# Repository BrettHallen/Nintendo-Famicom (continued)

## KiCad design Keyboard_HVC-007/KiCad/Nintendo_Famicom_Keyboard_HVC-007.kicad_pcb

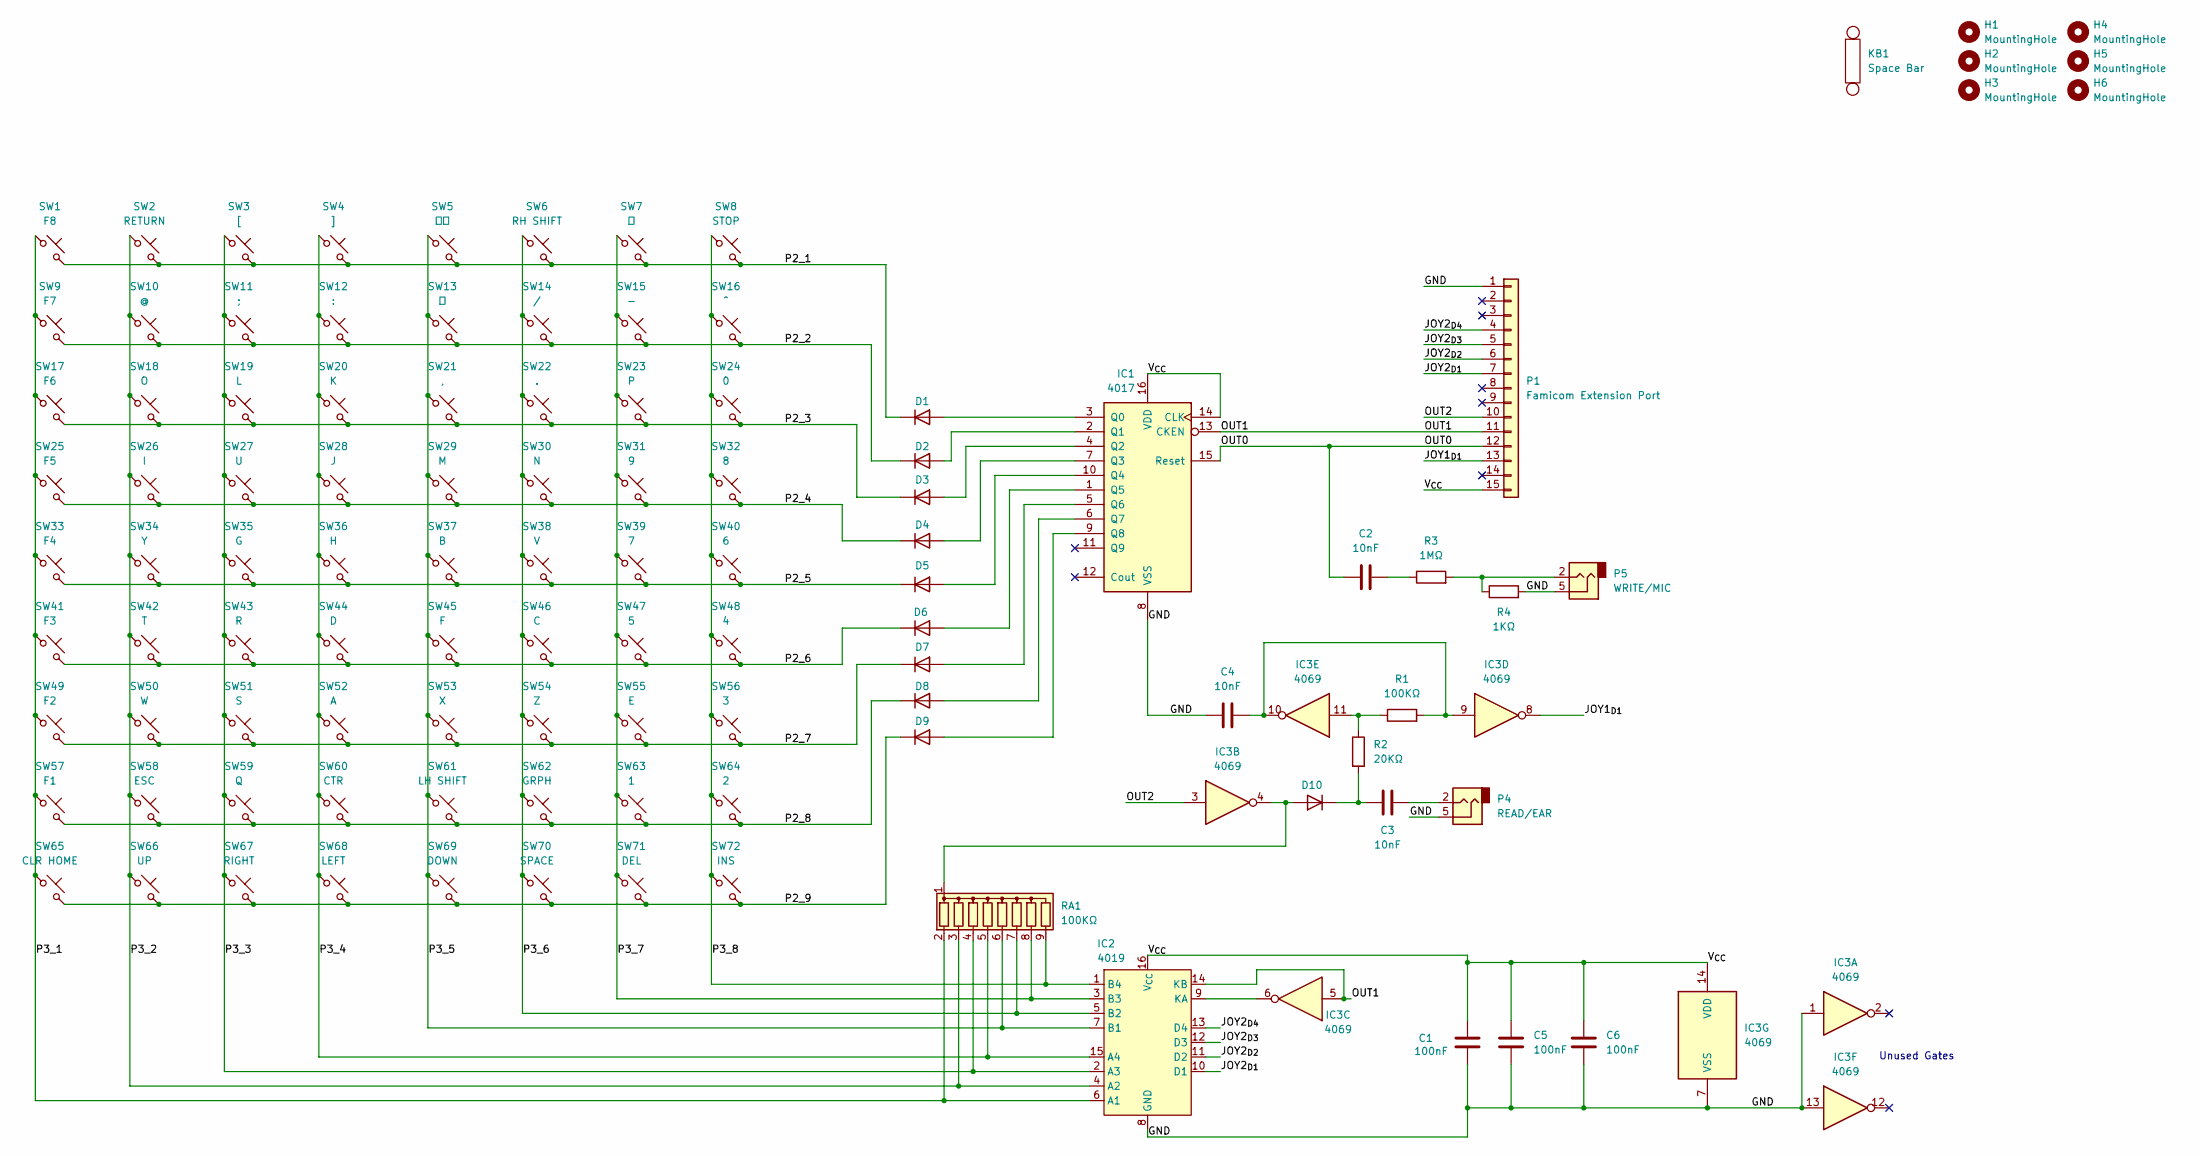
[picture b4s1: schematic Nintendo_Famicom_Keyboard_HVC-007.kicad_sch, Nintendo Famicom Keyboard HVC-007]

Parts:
C1, C5, C6: 100nF; C_Axial_L3.8mm_D2.6mm_P7.50mm_Horizontal
C2, C3, C4: 10nF; C_Axial_L3.8mm_D2.6mm_P7.50mm_Horizontal
D1, D2, D3, D4, D5, D6, D7, D8, D9, D10: 1N4148; D_DO-35_SOD27_P7.62mm_Horizontal
H1, H2, H3, H4, H5, H6: MountingHole; MountingHole_3.2mm_M3
IC1: 4017; DIP-16_W7.62mm
IC2: 4019; DIP-16_W7.62mm
IC3: 4069; DIP-14_W7.62mm
KB1: Space Bar; Stabilizer_Cherry_MX_7.00u
P1: Famicom Extension Port; 57478374
P4: READ/EAR; SJ3350820BTR
P5: WRITE/MIC; SJ3350820BTR
R1: 100KΩ; R_Axial_DIN0207_L6.3mm_D2.5mm_P10.16mm_Horizontal
R2: 20KΩ; R_Axial_DIN0207_L6.3mm_D2.5mm_P10.16mm_Horizontal
R3: 1MΩ; R_Axial_DIN0207_L6.3mm_D2.5mm_P10.16mm_Horizontal
R4: 1KΩ; R_Axial_DIN0207_L6.3mm_D2.5mm_P10.16mm_Horizontal
RA1: 100KΩ; R_Array_SIP9
SW1: F8; SW_Cherry_MX_PCB_2.00u
SW2: RETURN; SW_Cherry_MX_PCB_2.00u
SW3: [; SW_Cherry_MX_PCB_1.00u
SW4: ]; SW_Cherry_MX_PCB_1.00u
SW5: カナ; SW_Cherry_MX_PCB_1.00u
SW6: RH SHIFT; SW_Cherry_MX_PCB_2.00u
SW7: ￥; SW_Cherry_MX_PCB_1.00u
SW8: STOP; SW_Cherry_MX_PCB_1.00u
SW9: F7; SW_Cherry_MX_PCB_2.00u
SW10: @; SW_Cherry_MX_PCB_1.00u
SW11: ;; SW_Cherry_MX_PCB_1.00u
SW12: :; SW_Cherry_MX_PCB_1.00u
SW13: ン; SW_Cherry_MX_PCB_1.00u
SW14: /; SW_Cherry_MX_PCB_1.00u
SW15: -; SW_Cherry_MX_PCB_1.00u
SW16: ^; SW_Cherry_MX_PCB_1.00u
SW17: F6; SW_Cherry_MX_PCB_2.00u
SW18: O; SW_Cherry_MX_PCB_1.00u
SW19: L; SW_Cherry_MX_PCB_1.00u
SW20: K; SW_Cherry_MX_PCB_1.00u
SW21: ,; SW_Cherry_MX_PCB_1.00u
SW22: .; SW_Cherry_MX_PCB_1.00u
SW23: P; SW_Cherry_MX_PCB_1.00u
SW24: 0; SW_Cherry_MX_PCB_1.00u
SW25: F5; SW_Cherry_MX_PCB_2.00u
SW26: I; SW_Cherry_MX_PCB_1.00u
SW27: U; SW_Cherry_MX_PCB_1.00u
SW28: J; SW_Cherry_MX_PCB_1.00u
SW29: M; SW_Cherry_MX_PCB_1.00u
SW30: N; SW_Cherry_MX_PCB_1.00u
SW31: 9; SW_Cherry_MX_PCB_1.00u
SW32: 8; SW_Cherry_MX_PCB_1.00u
SW33: F4; SW_Cherry_MX_PCB_2.00u
SW34: Y; SW_Cherry_MX_PCB_1.00u
SW35: G; SW_Cherry_MX_PCB_1.00u
SW36: H; SW_Cherry_MX_PCB_1.00u
SW37: B; SW_Cherry_MX_PCB_1.00u
SW38: V; SW_Cherry_MX_PCB_1.00u
SW39: 7; SW_Cherry_MX_PCB_1.00u
SW40: 6; SW_Cherry_MX_PCB_1.00u
SW41: F3; SW_Cherry_MX_PCB_2.00u
SW42: T; SW_Cherry_MX_PCB_1.00u
SW43: R; SW_Cherry_MX_PCB_1.00u
SW44: D; SW_Cherry_MX_PCB_1.00u
SW45: F; SW_Cherry_MX_PCB_1.00u
SW46: C; SW_Cherry_MX_PCB_1.00u
SW47: 5; SW_Cherry_MX_PCB_1.00u
SW48: 4; SW_Cherry_MX_PCB_1.00u
SW49: F2; SW_Cherry_MX_PCB_2.00u
SW50: W; SW_Cherry_MX_PCB_1.00u
SW51: S; SW_Cherry_MX_PCB_1.00u
SW52: A; SW_Cherry_MX_PCB_1.00u
SW53: X; SW_Cherry_MX_PCB_1.00u
SW54: Z; SW_Cherry_MX_PCB_1.00u
SW55: E; SW_Cherry_MX_PCB_1.00u
SW56: 3; SW_Cherry_MX_PCB_1.00u
SW57: F1; SW_Cherry_MX_PCB_2.00u
SW58: ESC; SW_Cherry_MX_PCB_1.00u
SW59: Q; SW_Cherry_MX_PCB_1.00u
SW60: CTR; SW_Cherry_MX_PCB_1.00u
SW61: LH SHIFT; SW_Cherry_MX_PCB_2.00u
SW62: GRPH; SW_Cherry_MX_PCB_1.00u
SW63: 1; SW_Cherry_MX_PCB_1.00u
SW64: 2; SW_Cherry_MX_PCB_1.00u
SW65: CLR HOME; SW_Cherry_MX_PCB_1.00u
SW66: UP; SW_Cherry_MX_PCB_2.00u
SW67: RIGHT; SW_Cherry_MX_PCB_2.00u
SW68: LEFT; SW_Cherry_MX_PCB_2.00u
SW69: DOWN; SW_Cherry_MX_PCB_2.00u
SW70: SPACE; SW_Cherry_MX_PCB_7.00u
SW71: DEL; SW_Cherry_MX_PCB_1.00u
SW72: INS; SW_Cherry_MX_PCB_1.00u

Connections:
/GND: C1.2, C4.1, C5.2, C6.2, IC1.8 (VSS), IC2.8 (GND), IC3.1, IC3.7 (VSS), IC3.13, P1.1, P4.5, P5.5, R4.2
/JOY1_{D1}: IC3.8, P1.13
/JOY2_{D1}: IC2.10 (D1), P1.7
/JOY2_{D2}: IC2.11 (D2), P1.6
/JOY2_{D3}: IC2.12 (D3), P1.5
/JOY2_{D4}: IC2.13 (D4), P1.4
/OUT0: C2.1, IC1.15 (Reset), P1.12
/OUT1: IC1.13 (CKEN), IC2.14 (KB), IC3.5, P1.11
/OUT2: IC3.3, P1.10
/P2_1: D1.1 (K), SW1.2, SW2.2, SW3.2, SW4.2, SW5.2, SW6.2, SW7.2, SW8.2
/P2_2: D2.1 (K), SW9.2, SW10.2, SW11.2, SW12.2, SW13.2, SW14.2, SW15.2, SW16.2
/P2_3: D3.1 (K), SW17.2, SW18.2, SW19.2, SW20.2, SW21.2, SW22.2, SW23.2, SW24.2
/P2_4: D4.1 (K), SW25.2, SW26.2, SW27.2, SW28.2, SW29.2, SW30.2, SW31.2, SW32.2
/P2_5: D5.1 (K), SW33.2, SW34.2, SW35.2, SW36.2, SW37.2, SW38.2, SW39.2, SW40.2
/P2_6: D6.1 (K), SW41.2, SW42.2, SW43.2, SW44.2, SW45.2, SW46.2, SW47.2, SW48.2
/P2_7: D7.1 (K), SW49.2, SW50.2, SW51.2, SW52.2, SW53.2, SW54.2, SW55.2, SW56.2
/P2_8: D8.1 (K), SW57.2, SW58.2, SW59.2, SW60.2, SW61.2, SW62.2, SW63.2, SW64.2
/P2_9: D9.1 (K), SW65.2, SW66.2, SW67.2, SW68.2, SW69.2, SW70.2, SW71.2, SW72.2
/P3_1: IC2.6 (A1), RA1.2 (R1), SW1.1, SW9.1, SW17.1, SW25.1, SW33.1, SW41.1, SW49.1, SW57.1, SW65.1
/P3_2: IC2.4 (A2), RA1.3 (R2), SW2.1, SW10.1, SW18.1, SW26.1, SW34.1, SW42.1, SW50.1, SW58.1, SW66.1
/P3_3: IC2.2 (A3), RA1.4 (R3), SW3.1, SW11.1, SW19.1, SW27.1, SW35.1, SW43.1, SW51.1, SW59.1, SW67.1
/P3_4: IC2.15 (A4), RA1.5 (R4), SW4.1, SW12.1, SW20.1, SW28.1, SW36.1, SW44.1, SW52.1, SW60.1, SW68.1
/P3_5: IC2.7 (B1), RA1.6 (R5), SW5.1, SW13.1, SW21.1, SW29.1, SW37.1, SW45.1, SW53.1, SW61.1, SW69.1
/P3_6: IC2.5 (B2), RA1.7 (R6), SW6.1, SW14.1, SW22.1, SW30.1, SW38.1, SW46.1, SW54.1, SW62.1, SW70.1
/P3_7: IC2.3 (B3), RA1.8 (R7), SW7.1, SW15.1, SW23.1, SW31.1, SW39.1, SW47.1, SW55.1, SW63.1, SW71.1
/P3_8: IC2.1 (B4), RA1.9 (R8), SW8.1, SW16.1, SW24.1, SW32.1, SW40.1, SW48.1, SW56.1, SW64.1, SW72.1
/V_{CC}: C1.1, C5.1, C6.1, IC1.14 (CLK), IC1.16 (VDD), IC2.16 (V_{CC}), IC3.14 (VDD), P1.15
unnamed: C2.2, R3.1
unnamed: C3.2, P4.2
unnamed: C4.2, IC3.9, IC3.10, R1.2
unnamed: D1.2 (A), IC1.3 (Q0)
unnamed: D2.2 (A), IC1.2 (Q1)
unnamed: D3.2 (A), IC1.4 (Q2)
unnamed: D4.2 (A), IC1.7 (Q3)
unnamed: D5.2 (A), IC1.10 (Q4)
unnamed: D6.2 (A), IC1.1 (Q5)
unnamed: D7.2 (A), IC1.5 (Q6)
unnamed: D8.2 (A), IC1.6 (Q7)
unnamed: D9.2 (A), IC1.9 (Q8)
unnamed: D10.2 (A), IC3.4, RA1.1 (common)
unnamed: C3.1, D10.1 (K), R2.2
unnamed: IC2.9 (KA), IC3.6
unnamed: IC3.11, R1.1, R2.1
unnamed: P5.2, R3.2, R4.1

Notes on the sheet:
Unused Gates

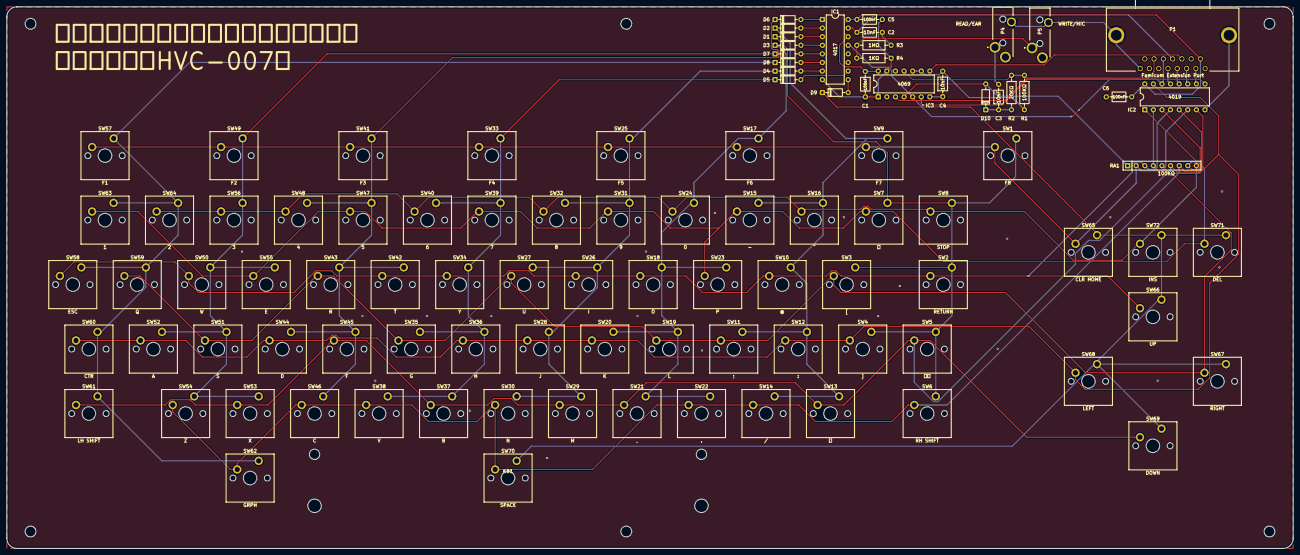
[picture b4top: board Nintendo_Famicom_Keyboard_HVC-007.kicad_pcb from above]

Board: 2 copper layers, 380.0 x 160.0 mm, 106 parts (0 on the bottom side), 44 nets.

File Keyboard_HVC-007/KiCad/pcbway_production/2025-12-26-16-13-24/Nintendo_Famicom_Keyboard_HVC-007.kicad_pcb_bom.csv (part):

Designator,Quantity,Value,Footprint,Package,MPN,DNP,Mount_Type,Description,Sim.Device,Sim.Pins
"C1, C5, C6",3,100nF,C_Axial_L3.8mm_D2.6mm_P7.50mm_Horizontal,,,,tht,Unpolarized capacitor,,
"C2, C3, C4",3,10nF,C_Axial_L3.8mm_D2.6mm_P7.50mm_Horizontal,,,,tht,Unpolarized capacitor,,
"D1, D10, D2, D3, D4, D5, D6, D7, D8, D9",10,1N4148,D_DO-35_SOD27_P7.62mm_Horizontal,,,,tht,Diode,D,1=K 2=A
IC1,1,4017,DIP-16_W7.62mm,,,,tht,Johnson Counter ( 10 outputs ),,
IC2,1,4019,DIP-16_W7.62mm,,,,tht,CMOS Quad AND/OR Select Gate,,
IC3,1,4069,DIP-14_W7.62mm,,,,tht,Hex inverter,,
KB1,1,Space Bar,Stabilizer_Cherry_MX_7.00u,,,,tht,,,
P1,1,Famicom Extension Port,57478374,,,,tht,"Generic connector, single row, 01x15, script generated (kicad-library-utils/schlib/autogen/connector/)",,
P4,1,READ/EAR,SJ3350820BTR,,,,tht,"Audio Jack, 2 Poles (Mono / TS)",,
P5,1,WRITE/MIC,SJ3350820BTR,,,,tht,"Audio Jack, 2 Poles (Mono / TS)",,
R1,1,100KΩ,R_Axial_DIN0207_L6.3mm_D2.5mm_P10.16mm_Horizontal,,,,tht,Resistor,,
R2,1,20KΩ,R_Axial_DIN0207_L6.3mm_D2.5mm_P10.16mm_Horizontal,,,,tht,Resistor,,
R3,1,1MΩ,R_Axial_DIN0207_L6.3mm_D2.5mm_P10.16mm_Horizontal,,,,tht,Resistor,,
R4,1,1KΩ,R_Axial_DIN0207_L6.3mm_D2.5mm_P10.16mm_Horizontal,,,,tht,Resistor,,
RA1,1,100KΩ,R_Array_SIP9,,,,tht,"8 resistor network, star topology, bussed resistors, small symbol",,
SW1,1,F8,SW_Cherry_MX_PCB_2.00u,,,,tht,"Push button switch, normally open, two pins, 45° tilted",,
SW10,1,@,SW_Cherry_MX_PCB_1.00u,,,,tht,"Push button switch, normally open, two pins, 45° tilted",,
SW11,1,;,SW_Cherry_MX_PCB_1.00u,,,,tht,"Push button switch, normally open, two pins, 45° tilted",,
SW12,1,:,SW_Cherry_MX_PCB_1.00u,,,,tht,"Push button switch, normally open, two pins, 45° tilted",,
SW13,1,ン,SW_Cherry_MX_PCB_1.00u,,,,tht,"Push button switch, normally open, two pins, 45° tilted",,
SW14,1,/,SW_Cherry_MX_PCB_1.00u,,,,tht,"Push button switch, normally open, two pins, 45° tilted",,
SW15,1,-,SW_Cherry_MX_PCB_1.00u,,,,tht,"Push button switch, normally open, two pins, 45° tilted",,
SW16,1,^,SW_Cherry_MX_PCB_1.00u,,,,tht,"Push button switch, normally open, two pins, 45° tilted",,
SW17,1,F6,SW_Cherry_MX_PCB_2.00u,,,,tht,"Push button switch, normally open, two pins, 45° tilted",,
SW18,1,O,SW_Cherry_MX_PCB_1.00u,,,,tht,"Push button switch, normally open, two pins, 45° tilted",,
SW19,1,L,SW_Cherry_MX_PCB_1.00u,,,,tht,"Push button switch, normally open, two pins, 45° tilted",,
SW2,1,RET,SW_Cherry_MX_PCB_2.00u,,,,tht,"Push button switch, normally open, two pins, 45° tilted",,
SW20,1,K,SW_Cherry_MX_PCB_1.00u,,,,tht,"Push button switch, normally open, two pins, 45° tilted",,
SW21,1,",",SW_Cherry_MX_PCB_1.00u,,,,tht,"Push button switch, normally open, two pins, 45° tilted",,
SW22,1,.,SW_Cherry_MX_PCB_1.00u,,,,tht,"Push button switch, normally open, two pins, 45° tilted",,
SW23,1,P,SW_Cherry_MX_PCB_1.00u,,,,tht,"Push button switch, normally open, two pins, 45° tilted",,
SW24,1,0,SW_Cherry_MX_PCB_1.00u,,,,tht,"Push button switch, normally open, two pins, 45° tilted",,
SW25,1,F5,SW_Cherry_MX_PCB_2.00u,,,,tht,"Push button switch, normally open, two pins, 45° tilted",,
SW26,1,I,SW_Cherry_MX_PCB_1.00u,,,,tht,"Push button switch, normally open, two pins, 45° tilted",,
SW27,1,U,SW_Cherry_MX_PCB_1.00u,,,,tht,"Push button switch, normally open, two pins, 45° tilted",,
SW28,1,J,SW_Cherry_MX_PCB_1.00u,,,,tht,"Push button switch, normally open, two pins, 45° tilted",,
SW29,1,M,SW_Cherry_MX_PCB_1.00u,,,,tht,"Push button switch, normally open, two pins, 45° tilted",,
SW3,1,[,SW_Cherry_MX_PCB_1.00u,,,,tht,"Push button switch, normally open, two pins, 45° tilted",,
SW30,1,N,SW_Cherry_MX_PCB_1.00u,,,,tht,"Push button switch, normally open, two pins, 45° tilted",,
SW31,1,9,SW_Cherry_MX_PCB_1.00u,,,,tht,"Push button switch, normally open, two pins, 45° tilted",,
SW32,1,8,SW_Cherry_MX_PCB_1.00u,,,,tht,"Push button switch, normally open, two pins, 45° tilted",,
SW33,1,F4,SW_Cherry_MX_PCB_2.00u,,,,tht,"Push button switch, normally open, two pins, 45° tilted",,
SW34,1,Y,SW_Cherry_MX_PCB_1.00u,,,,tht,"Push button switch, normally open, two pins, 45° tilted",,
SW35,1,G,SW_Cherry_MX_PCB_1.00u,,,,tht,"Push button switch, normally open, two pins, 45° tilted",,
SW36,1,H,SW_Cherry_MX_PCB_1.00u,,,,tht,"Push button switch, normally open, two pins, 45° tilted",,
SW37,1,B,SW_Cherry_MX_PCB_1.00u,,,,tht,"Push button switch, normally open, two pins, 45° tilted",,
SW38,1,V,SW_Cherry_MX_PCB_1.00u,,,,tht,"Push button switch, normally open, two pins, 45° tilted",,
SW39,1,7,SW_Cherry_MX_PCB_1.00u,,,,tht,"Push button switch, normally open, two pins, 45° tilted",,
SW4,1,],SW_Cherry_MX_PCB_1.00u,,,,tht,"Push button switch, normally open, two pins, 45° tilted",,
SW40,1,6,SW_Cherry_MX_PCB_1.00u,,,,tht,"Push button switch, normally open, two pins, 45° tilted",,
SW41,1,F3,SW_Cherry_MX_PCB_2.00u,,,,tht,"Push button switch, normally open, two pins, 45° tilted",,
SW42,1,T,SW_Cherry_MX_PCB_1.00u,,,,tht,"Push button switch, normally open, two pins, 45° tilted",,
SW43,1,R,SW_Cherry_MX_PCB_1.00u,,,,tht,"Push button switch, normally open, two pins, 45° tilted",,
SW44,1,D,SW_Cherry_MX_PCB_1.00u,,,,tht,"Push button switch, normally open, two pins, 45° tilted",,
SW45,1,F,SW_Cherry_MX_PCB_1.00u,,,,tht,"Push button switch, normally open, two pins, 45° tilted",,
SW46,1,C,SW_Cherry_MX_PCB_1.00u,,,,tht,"Push button switch, normally open, two pins, 45° tilted",,
SW47,1,5,SW_Cherry_MX_PCB_1.00u,,,,tht,"Push button switch, normally open, two pins, 45° tilted",,
SW48,1,4,SW_Cherry_MX_PCB_1.00u,,,,tht,"Push button switch, normally open, two pins, 45° tilted",,
SW49,1,F2,SW_Cherry_MX_PCB_2.00u,,,,tht,"Push button switch, normally open, two pins, 45° tilted",,
SW5,1,カナ,SW_Cherry_MX_PCB_1.00u,,,,tht,"Push button switch, normally open, two pins, 45° tilted",,
SW50,1,W,SW_Cherry_MX_PCB_1.00u,,,,tht,"Push button switch, normally open, two pins, 45° tilted",,
SW51,1,S,SW_Cherry_MX_PCB_1.00u,,,,tht,"Push button switch, normally open, two pins, 45° tilted",,
SW52,1,A,SW_Cherry_MX_PCB_1.00u,,,,tht,"Push button switch, normally open, two pins, 45° tilted",,
SW53,1,X,SW_Cherry_MX_PCB_1.00u,,,,tht,"Push button switch, normally open, two pins, 45° tilted",,
SW54,1,Z,SW_Cherry_MX_PCB_1.00u,,,,tht,"Push button switch, normally open, two pins, 45° tilted",,
SW55,1,E,SW_Cherry_MX_PCB_1.00u,,,,tht,"Push button switch, normally open, two pins, 45° tilted",,
SW56,1,3,SW_Cherry_MX_PCB_1.00u,,,,tht,"Push button switch, normally open, two pins, 45° tilted",,
SW57,1,F1,SW_Cherry_MX_PCB_2.00u,,,,tht,"Push button switch, normally open, two pins, 45° tilted",,
SW58,1,ESC,SW_Cherry_MX_PCB_1.00u,,,,tht,"Push button switch, normally open, two pins, 45° tilted",,
SW59,1,Q,SW_Cherry_MX_PCB_1.00u,,,,tht,"Push button switch, normally open, two pins, 45° tilted",,
SW6,1,RH SHIFT,SW_Cherry_MX_PCB_2.00u,,,,tht,"Push button switch, normally open, two pins, 45° tilted",,
SW60,1,CTR,SW_Cherry_MX_PCB_1.00u,,,,tht,"Push button switch, normally open, two pins, 45° tilted",,
SW61,1,LH SHIFT,SW_Cherry_MX_PCB_2.00u,,,,tht,"Push button switch, normally open, two pins, 45° tilted",,
SW62,1,GRPH,SW_Cherry_MX_PCB_1.00u,,,,tht,"Push button switch, normally open, two pins, 45° tilted",,
SW63,1,1,SW_Cherry_MX_PCB_1.00u,,,,tht,"Push button switch, normally open, two pins, 45° tilted",,
SW64,1,2,SW_Cherry_MX_PCB_1.00u,,,,tht,"Push button switch, normally open, two pins, 45° tilted",,
SW65,1,CLR HOME,SW_Cherry_MX_PCB_1.00u,,,,tht,"Push button switch, normally open, two pins, 45° tilted",,
SW66,1,UP,SW_Cherry_MX_PCB_2.00u,,,,tht,"Push button switch, normally open, two pins, 45° tilted",,
SW67,1,RIGHT,SW_Cherry_MX_PCB_2.00u,,,,tht,"Push button switch, normally open, two pins, 45° tilted",,
SW68,1,LEFT,SW_Cherry_MX_PCB_2.00u,,,,tht,"Push button switch, normally open, two pins, 45° tilted",,
SW69,1,DOWN,SW_Cherry_MX_PCB_2.00u,,,,tht,"Push button switch, normally open, two pins, 45° tilted",,
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
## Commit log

2025-12-24 Update README.md
    Added explanatory text from Archive page.
2025-12-25 Initial keyboard schematic done
2025-12-25 PCB design started
2025-12-25 Additional images
2025-12-26 PCB design progress
2025-12-26 Initial PCB layout completed
2025-12-26 3D PCB representation
2025-12-26 Updated value text visibility
2025-12-27 Schematic started
2025-12-27 Schematic design progression
2025-12-27 Initial schematic completed
2025-12-27 Added DIP switch for RAM bank selection
2025-12-27 PCB layout started
2025-12-28 PCB design continues
2025-12-28 Additional silkscreen text
2025-12-30 Renaming files
2025-12-30 Finalised initial Rev. A design
2025-12-31 Minor cosmetic PCB changes
2025-12-31 Only one button cell holder needed
    Each CR2032 button cell is 3V, duh, so only one needed to replace the 2xAA cells.
2026-01-01 Initial schematic drawn
2026-01-01 Folder renamed
2026-01-05 Renamed L/R signals
2026-01-06 Images of HVC-051 controller
2026-01-06 Minor changes to schematic
2026-01-07 Corrected W545 pinout
2026-01-07 Added original cartridge images
2026-01-07 Patching ROM for 8KB RAM support
2026-01-08 Added some v2.1A patches
2026-01-08 Added extra patching (REM bugfix, v3.1 version)
2026-01-08 Captured signalling
2026-01-11 Switchable BASIC version with 27512
2026-01-11 Switched PRG ROM to 27512
    Switch between v2.1 and v3.0 Family BASIC
2026-01-11 Reorganised KiCad folders
2026-01-11 v3 PCB has extra diode compared to v2 board
2026-01-12 Reorganise folders
2026-01-12 Making sure I don't accidentally commit a ROM file :)
2026-01-12 Added patching for NES-header ROM
2026-01-12 Modifying CRC values
2026-01-12 Added "FBv30_merge":"Family BASIC v3.0 (PRG+CHR)"
2026-01-12 Added NES 2.0 header support in patching
    Family BASIC v2.1 2KB header: 4E 45 53 1A 02 01 03 08 00 00 50 00 00 00 00 23
    Family BASIC v2.1 8KB header: 4E 45 53 1A 02 01 03 08 00 00 70 00 00 00 00 23 (?)
    Family BASIC v3.0 4KB header: 4E 45 53 1A 02 01 03 08 00 00 60 00 00 00 00 23
    Family BASIC v3.0 8KB header: 4E 45 53 1A 02 01 03 08 00 00 70 00 00 00 00 23 (?)
2026-01-12 Problem with v2.1A patches
    My v2.1A ROM dump might not be correct - its CRC32 checksum doesn't match known-good dumps. Will have to try re-dumping.
2026-01-12 Added v1.0 checking (no patching though)
2026-01-13 Added possible RENUM bug fix
2026-01-13 FBv3 RENUM bug fix
2026-01-13 Added -0 overflow error bug fix
2026-01-14 Added tested v2.1A 8KB patching
2026-01-15 Initial commit of disassembly
2026-01-15 Don't accidentally commit ROMs
2026-01-15 Updated checksums & removed unneeded byte patch [RENUM]
    >> Input ROM checksum: 0x6BA08175
    >> Detected: Family BASIC v3.0 (PRG+CHR+NES 2.0 header)
    >> Applying single-byte patches:
    Patching 0x000A: 0x60 → 0x70 [NES 2.0 header 4KB->8KB]
    Patching 0x06B4: 0x6F → 0x7F [Increase RAM limit from 0x6C00 to 0x7C00]
    Patching 0x17E8: 0x70 → 0x80 [Increase RAM limit from 0x6C00 to 0x7C00]
2026-06-22 Initial commit
    First attempt at adapting decrazyo's ANES Dual PPU for the Famicom
2026-06-22 Minor tidying up
2026-06-23 Moved decoupling capacitor
